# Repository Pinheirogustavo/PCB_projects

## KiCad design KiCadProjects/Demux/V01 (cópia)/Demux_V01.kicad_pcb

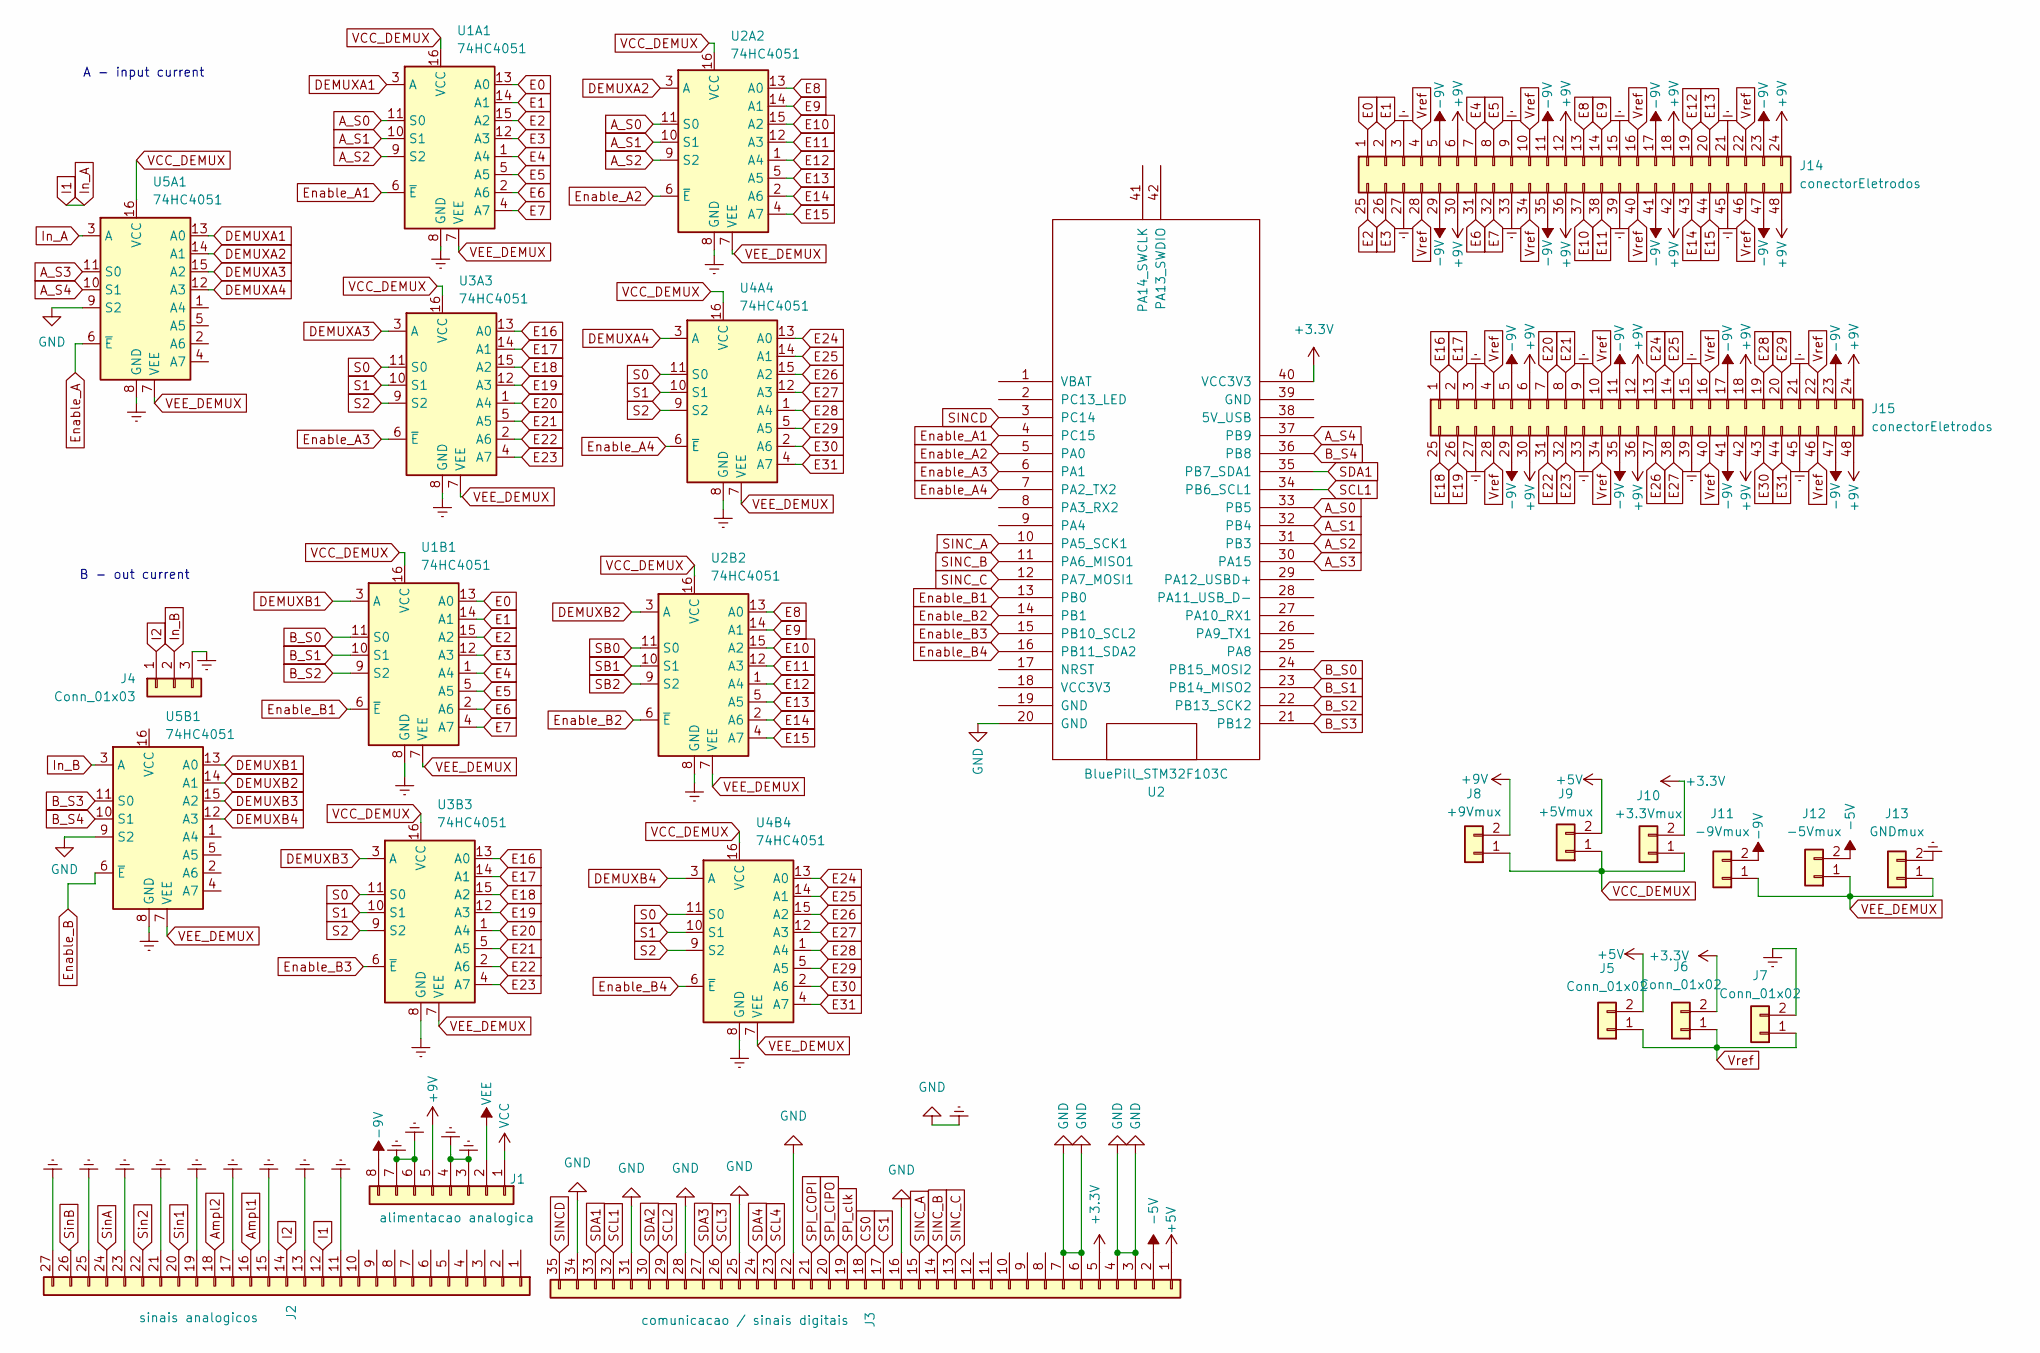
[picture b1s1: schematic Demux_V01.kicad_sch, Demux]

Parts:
J1: alimentacao analogica; PinHeader_1x08_P2.54mm_Vertical
J2: sinais analogicos; PinHeader_1x27_P2.54mm_Vertical
J3: comunicacao / sinais digitais; PinHeader_1x35_P2.54mm_Vertical
J4: Conn_01x03; PinHeader_1x03_P2.54mm_Vertical
J5, J6, J7: Conn_01x02; PinHeader_1x02_P2.54mm_Vertical
J8: +9Vmux; PinHeader_1x02_P2.54mm_Vertical
J9: +5Vmux; PinHeader_1x02_P2.54mm_Vertical
J10: +3.3Vmux; PinHeader_1x02_P2.54mm_Vertical
J11: -9Vmux; PinHeader_1x02_P2.54mm_Vertical
J12: -5Vmux; PinHeader_1x02_P2.54mm_Vertical
J13: GNDmux; PinHeader_1x02_P2.54mm_Vertical
J14, J15: conectorEletrodos; PinHeader_2x24_P2.54mm_Vertical
U1A1, U1B1, U2A2, U2B2, U3A3, U3B3, U4A4, U4B4, U5A1, U5B1: 74HC4051; N16
U2: BluePill_STM32F103C

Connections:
+3.3V: J3.5, J6.2, J10.2, U2.40 (VCC3V3)
+5V: J3.1, J5.2, J9.2
+9V: J1.5, J8.2, J14.6, J14.12, J14.18, J14.24, J14.30, J14.36, J14.42, J14.48, J15.6, J15.12, J15.18, J15.24, J15.30, J15.36, J15.42, J15.48
-5V: J3.2, J12.2
-9V: J1.8, J11.2, J14.5, J14.11, J14.17, J14.23, J14.29, J14.35, J14.41, J14.47, J15.5, J15.11, J15.17, J15.23, J15.29, J15.35, J15.41, J15.47
A_S0: U1A1.11 (S0), U2.33 (PB5), U2A2.11 (S0)
A_S1: U1A1.10 (S1), U2.32 (PB4), U2A2.10 (S1)
A_S2: U1A1.9 (S2), U2.31 (PB3), U2A2.9 (S2)
A_S3: U2.30 (PA15), U5A1.11 (S0)
A_S4: U2.37 (PB9), U5A1.10 (S1)
Ampl1: J2.16
Ampl2: J2.18
B_S0: U1B1.11 (S0), U2.24 (PB15_MOSI2)
B_S1: U1B1.10 (S1), U2.23 (PB14_MISO2)
B_S2: U1B1.9 (S2), U2.22 (PB13_SCK2)
B_S3: U2.21 (PB12), U5B1.11 (S0)
B_S4: U2.36 (PB8), U5B1.10 (S1)
CS0: J3.18
CS1: J3.17
DEMUXA1: U1A1.3 (A), U5A1.13 (A0)
DEMUXA2: U2A2.3 (A), U5A1.14 (A1)
DEMUXA3: U3A3.3 (A), U5A1.15 (A2)
DEMUXA4: U4A4.3 (A), U5A1.12 (A3)
DEMUXB1: U1B1.3 (A), U5B1.13 (A0)
DEMUXB2: U2B2.3 (A), U5B1.14 (A1)
DEMUXB3: U3B3.3 (A), U5B1.15 (A2)
DEMUXB4: U4B4.3 (A), U5B1.12 (A3)
E0: J14.1, U1A1.13 (A0), U1B1.13 (A0)
E1: J14.2, U1A1.14 (A1), U1B1.14 (A1)
E2: J14.25, U1A1.15 (A2), U1B1.15 (A2)
E3: J14.26, U1A1.12 (A3), U1B1.12 (A3)
E4: J14.7, U1A1.1 (A4), U1B1.1 (A4)
E5: J14.8, U1A1.5 (A5), U1B1.5 (A5)
E6: J14.31, U1A1.2 (A6), U1B1.2 (A6)
E7: J14.32, U1A1.4 (A7), U1B1.4 (A7)
E8: J14.13, U2A2.13 (A0), U2B2.13 (A0)
E9: J14.14, U2A2.14 (A1), U2B2.14 (A1)
E10: J14.37, U2A2.15 (A2), U2B2.15 (A2)
E11: J14.38, U2A2.12 (A3), U2B2.12 (A3)
E12: J14.19, U2A2.1 (A4), U2B2.1 (A4)
E13: J14.20, U2A2.5 (A5), U2B2.5 (A5)
E14: J14.43, U2A2.2 (A6), U2B2.2 (A6)
E15: J14.44, U2A2.4 (A7), U2B2.4 (A7)
E16: J15.1, U3A3.13 (A0), U3B3.13 (A0)
E17: J15.2, U3A3.14 (A1), U3B3.14 (A1)
E18: J15.25, U3A3.15 (A2), U3B3.15 (A2)
E19: J15.26, U3A3.12 (A3), U3B3.12 (A3)
E20: J15.7, U3A3.1 (A4), U3B3.1 (A4)
E21: J15.8, U3A3.5 (A5), U3B3.5 (A5)
E22: J15.31, U3A3.2 (A6), U3B3.2 (A6)
E23: J15.32, U3A3.4 (A7), U3B3.4 (A7)
E24: J15.13, U4A4.13 (A0), U4B4.13 (A0)
E25: J15.14, U4A4.14 (A1), U4B4.14 (A1)
E26: J15.37, U4A4.15 (A2), U4B4.15 (A2)
E27: J15.38, U4A4.12 (A3), U4B4.12 (A3)
E28: J15.19, U4A4.1 (A4), U4B4.1 (A4)
E29: J15.20, U4A4.5 (A5), U4B4.5 (A5)
E30: J15.43, U4A4.2 (A6), U4B4.2 (A6)
E31: J15.44, U4A4.4 (A7), U4B4.4 (A7)
Earth: J1.3, J1.4, J1.6, J1.7, J2.11, J2.13, J2.15, J2.17, J2.19, J2.21, J2.23, J2.25, J2.27, J3.3, J3.4, J3.6, J3.7, J3.16, J3.22, J3.25, J3.28, J3.31, J3.34, J4.3, J7.2, J13.2, J14.3, J14.9, J14.15, J14.21, J14.27, J14.33, J14.39, J14.45, J15.3, J15.9, J15.15, J15.21, J15.27, J15.33, J15.39, J15.45, U1A1.8 (GND), U1B1.8 (GND), U2.20 (GND), U2A2.8 (GND), U2B2.8 (GND), U3A3.8 (GND), U3B3.8 (GND), U4A4.8 (GND), U4B4.8 (GND), U5A1.8 (GND), U5A1.9 (S2), U5B1.8 (GND), U5B1.9 (S2)
Enable_A: U5A1.6 (~E)
Enable_A1: U1A1.6 (~E), U2.4 (PC15)
Enable_A2: U2.5 (PA0), U2A2.6 (~E)
Enable_A3: U2.6 (PA1), U3A3.6 (~E)
Enable_A4: U2.7 (PA2_TX2), U4A4.6 (~E)
Enable_B: U5B1.6 (~E)
Enable_B1: U1B1.6 (~E), U2.13 (PB0)
Enable_B2: U2.14 (PB1), U2B2.6 (~E)
Enable_B3: U2.15 (PB10_SCL2), U3B3.6 (~E)
Enable_B4: U2.16 (PB11_SDA2), U4B4.6 (~E)
I1: J2.12, U5A1.3 (A)
I2: J2.14, J4.1
In_B: J4.2, U5B1.3 (A)
S0: U3A3.11 (S0), U3B3.11 (S0), U4A4.11 (S0), U4B4.11 (S0)
S1: U3A3.10 (S1), U3B3.10 (S1), U4A4.10 (S1), U4B4.10 (S1)
S2: U3A3.9 (S2), U3B3.9 (S2), U4A4.9 (S2), U4B4.9 (S2)
SB0: U2B2.11 (S0)
SB1: U2B2.10 (S1)
SB2: U2B2.9 (S2)
SCL1: J3.32, U2.34 (PB6_SCL1)
SCL2: J3.29
SCL3: J3.26
SCL4: J3.23
SDA1: J3.33, U2.35 (PB7_SDA1)
SDA2: J3.30
SDA3: J3.27
SDA4: J3.24
SINCD: J3.35, U2.3 (PC14)
SINC_A: J3.15, U2.10 (PA5_SCK1)
SINC_B: J3.14, U2.11 (PA6_MISO1)
SINC_C: J3.13, U2.12 (PA7_MOSI1)
SPI_CIPO: J3.20
SPI_COPI: J3.21
SPI_clk: J3.19
Sin1: J2.20
Sin2: J2.22
SinA: J2.24
SinB: J2.26
VCC: J1.1
VCC_DEMUX: J8.1, J9.1, J10.1, U1A1.16 (VCC), U1B1.16 (VCC), U2A2.16 (VCC), U2B2.16 (VCC), U3A3.16 (VCC), U3B3.16 (VCC), U4A4.16 (VCC), U4B4.16 (VCC), U5A1.16 (VCC)
VEE: J1.2
VEE_DEMUX: J11.1, J12.1, J13.1, U1A1.7 (VEE), U1B1.7 (VEE), U2A2.7 (VEE), U2B2.7 (VEE), U3A3.7 (VEE), U3B3.7 (VEE), U4A4.7 (VEE), U4B4.7 (VEE), U5A1.7 (VEE), U5B1.7 (VEE)
Vref: J5.1, J6.1, J7.1, J14.4, J14.10, J14.16, J14.22, J14.28, J14.34, J14.40, J14.46, J15.4, J15.10, J15.16, J15.22, J15.28, J15.34, J15.40, J15.46

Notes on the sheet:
A - input current
B - out current

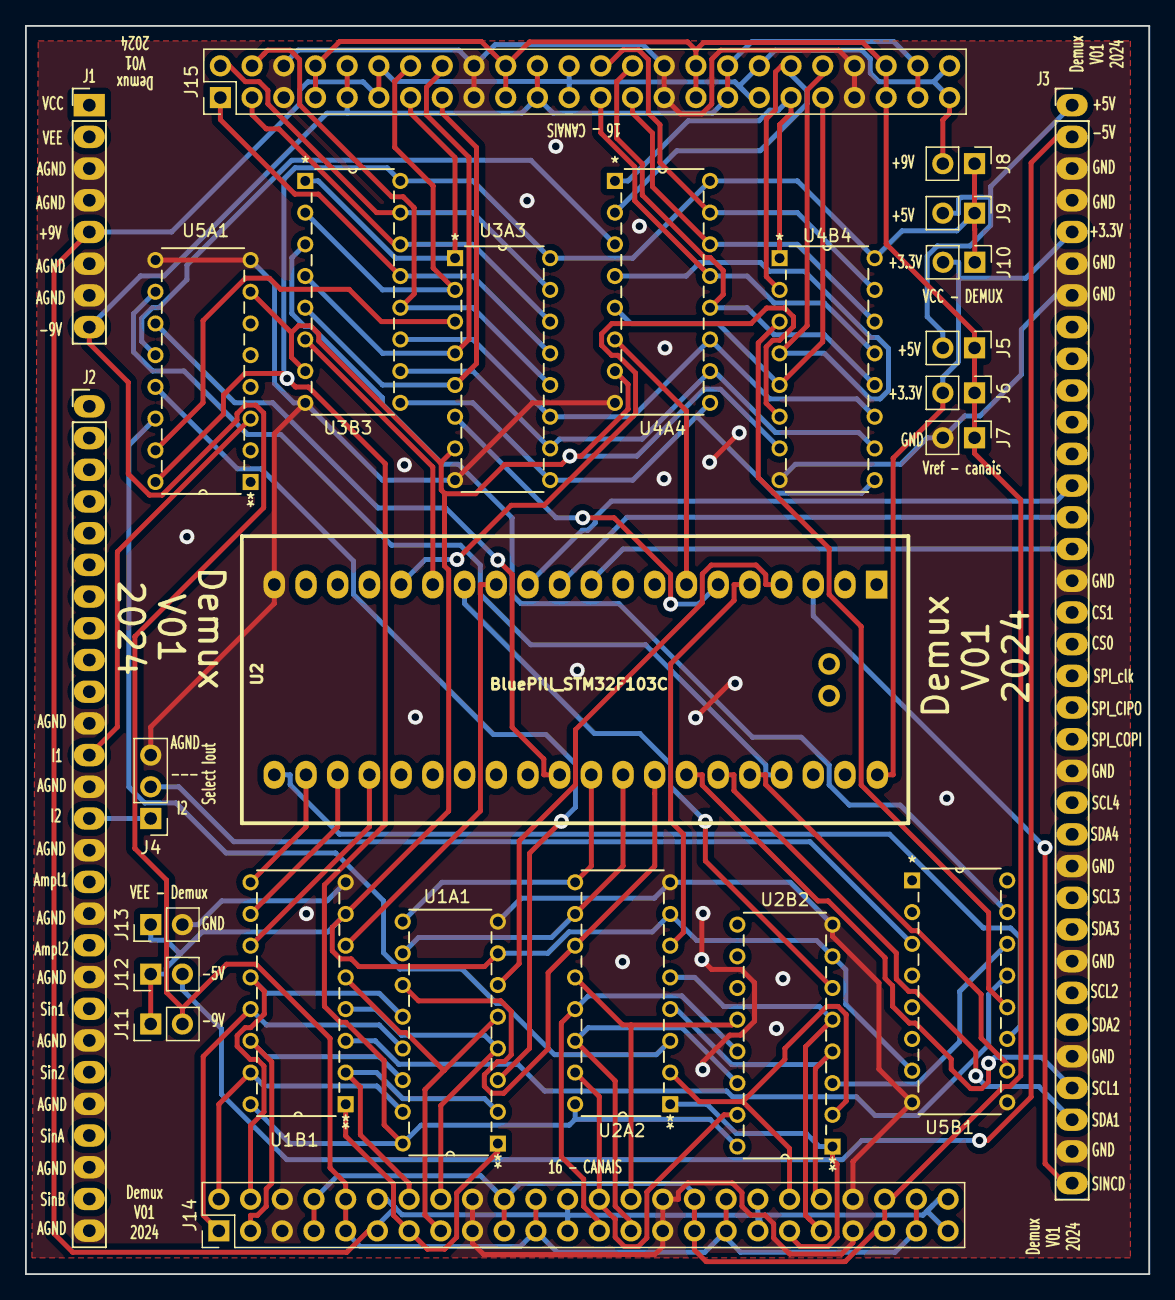
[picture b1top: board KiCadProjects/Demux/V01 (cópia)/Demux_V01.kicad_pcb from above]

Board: 2 copper layers, 90.0 x 100.0 mm, 26 parts (0 on the bottom side), 79 nets.

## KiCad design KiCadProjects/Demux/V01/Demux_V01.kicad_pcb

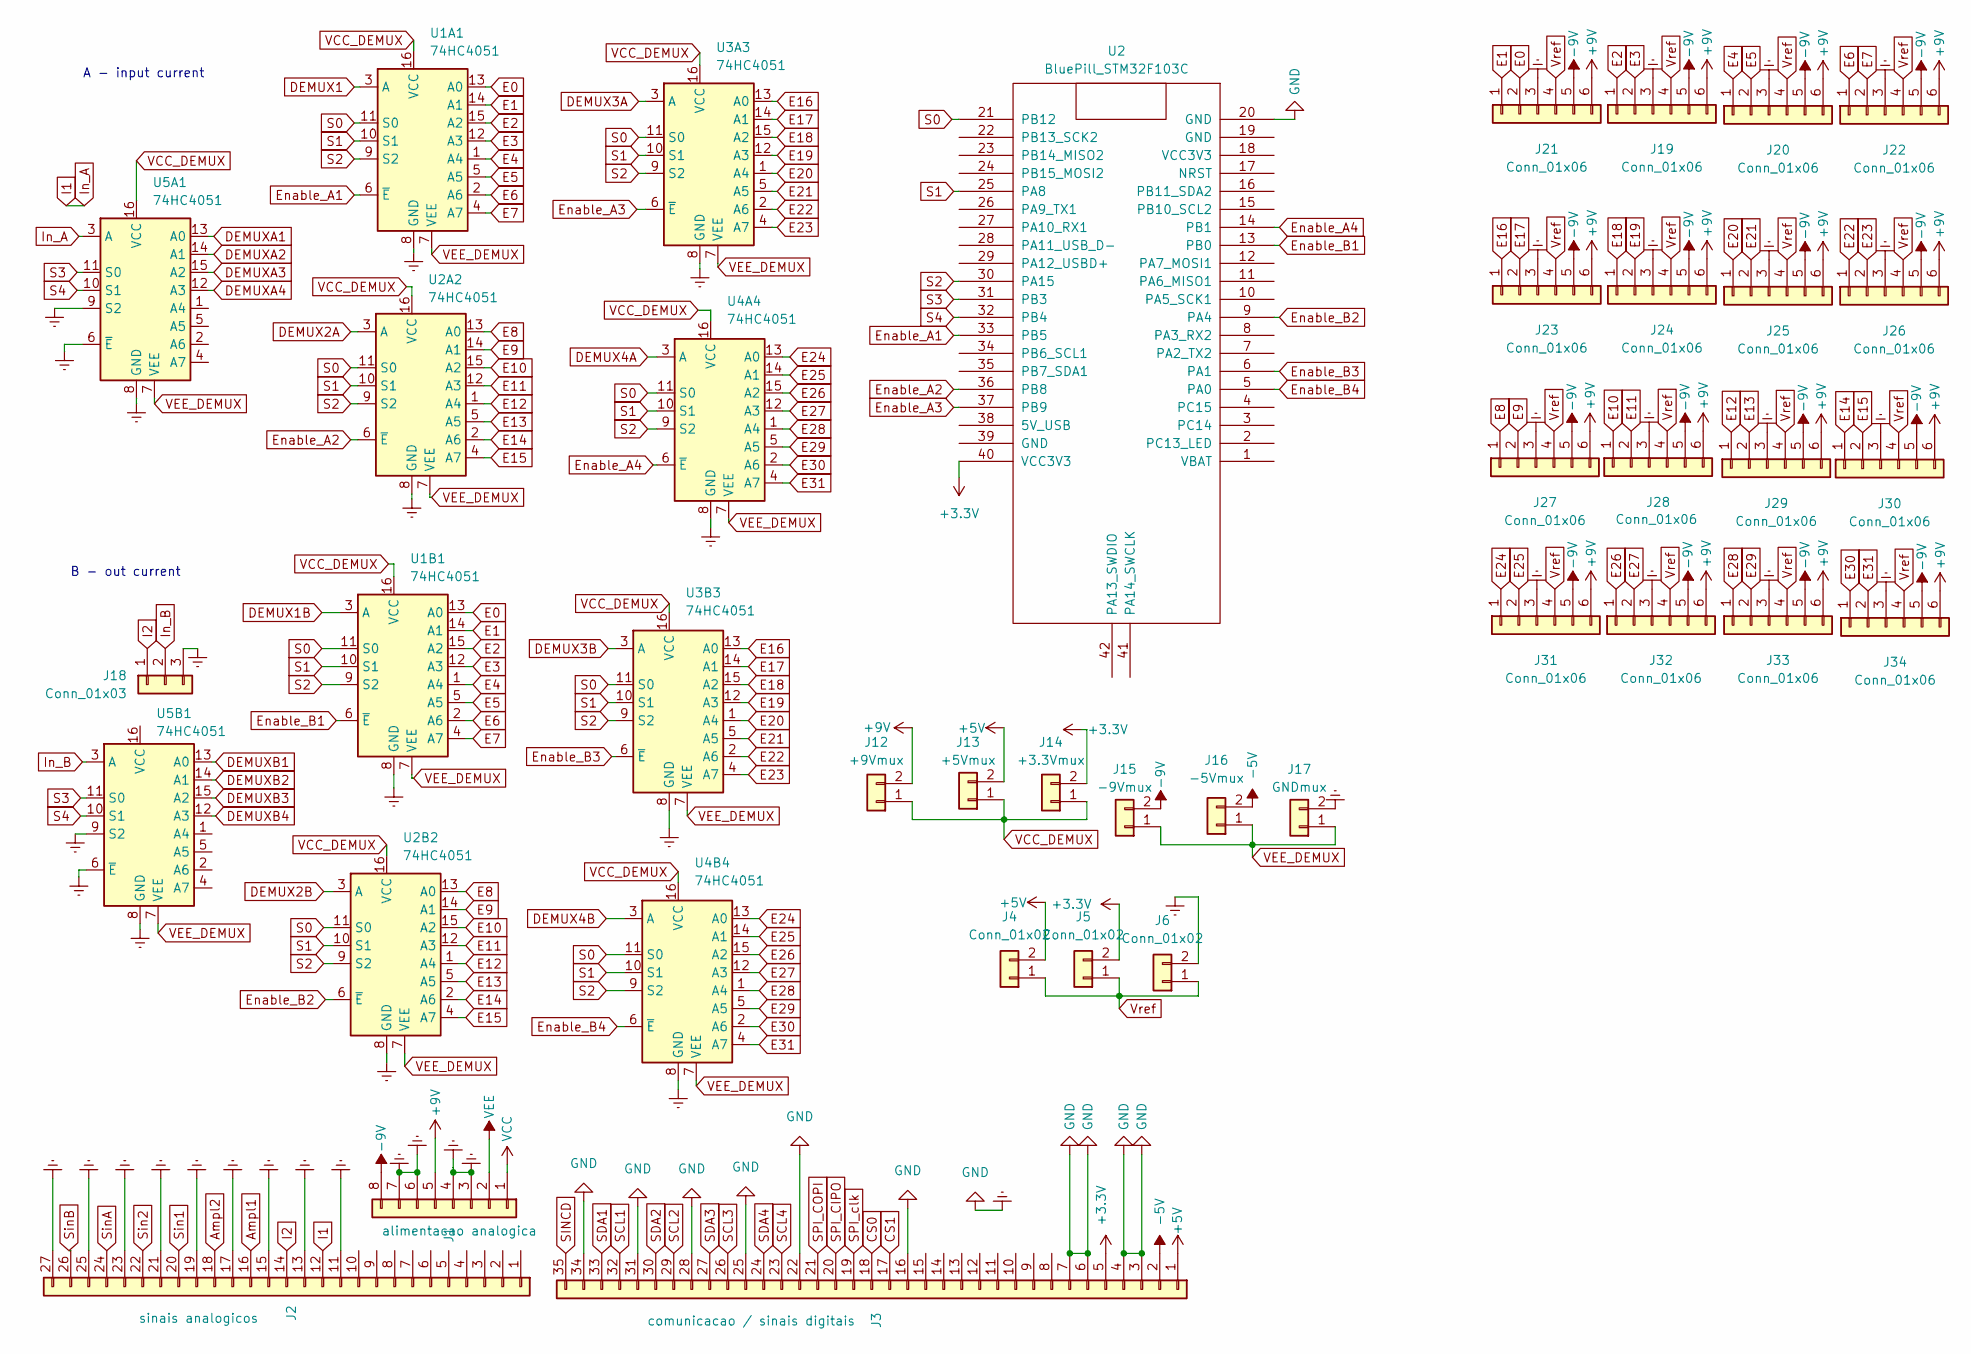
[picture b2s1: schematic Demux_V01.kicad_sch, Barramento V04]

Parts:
J1: alimentacao analogica; PinHeader_1x08_P2.54mm_Vertical
J2: sinais analogicos; PinHeader_1x27_P2.54mm_Vertical
J3: comunicacao / sinais digitais; PinHeader_1x35_P2.54mm_Vertical
J4, J5, J6: Conn_01x02; PinHeader_1x02_P2.54mm_Vertical
J12: +9Vmux; PinHeader_1x02_P2.54mm_Vertical
J13: +5Vmux; PinHeader_1x02_P2.54mm_Vertical
J14: +3.3Vmux; PinHeader_1x02_P2.54mm_Vertical
J15: -9Vmux; PinHeader_1x02_P2.54mm_Vertical
J16: -5Vmux; PinHeader_1x02_P2.54mm_Vertical
J17: GNDmux; PinHeader_1x02_P2.54mm_Vertical
J18: Conn_01x03; PinHeader_1x03_P2.54mm_Vertical
J19, J20, J21, J22, J23, J24, J25, J26, J27, J28, J29, J30, J31, J32, J33, J34: Conn_01x06; PinHeader_1x06_P2.54mm_Horizontal
U1A1, U1B1, U2A2, U2B2, U3A3, U3B3, U4A4, U4B4, U5A1, U5B1: 74HC4051; N16
U2: BluePill_STM32F103C

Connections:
+3.3V: J3.5, J5.2, J14.2, U2.40 (VCC3V3)
+5V: J3.1, J4.2, J13.2
+9V: J1.5, J12.2, J19.6, J20.6, J21.6, J22.6, J23.6, J24.6, J25.6, J26.6, J27.6, J28.6, J29.6, J30.6, J31.6, J32.6, J33.6, J34.6
-5V: J3.2, J16.2
-9V: J1.8, J15.2, J19.5, J20.5, J21.5, J22.5, J23.5, J24.5, J25.5, J26.5, J27.5, J28.5, J29.5, J30.5, J31.5, J32.5, J33.5, J34.5
Ampl1: J2.16
Ampl2: J2.18
CS0: J3.18
CS1: J3.17
DEMUX1: U1A1.3 (A)
DEMUX1B: U1B1.3 (A)
DEMUX2A: U2A2.3 (A)
DEMUX2B: U2B2.3 (A)
DEMUX3A: U3A3.3 (A)
DEMUX3B: U3B3.3 (A)
DEMUX4A: U4A4.3 (A)
DEMUX4B: U4B4.3 (A)
DEMUXA1: U5A1.13 (A0)
DEMUXA2: U5A1.14 (A1)
DEMUXA3: U5A1.15 (A2)
DEMUXA4: U5A1.12 (A3)
DEMUXB1: U5B1.13 (A0)
DEMUXB2: U5B1.14 (A1)
DEMUXB3: U5B1.15 (A2)
DEMUXB4: U5B1.12 (A3)
E0: J21.2, U1A1.13 (A0), U1B1.13 (A0)
E1: J21.1, U1A1.14 (A1), U1B1.14 (A1)
E2: J19.1, U1A1.15 (A2), U1B1.15 (A2)
E3: J19.2, U1A1.12 (A3), U1B1.12 (A3)
E4: J20.1, U1A1.1 (A4), U1B1.1 (A4)
E5: J20.2, U1A1.5 (A5), U1B1.5 (A5)
E6: J22.1, U1A1.2 (A6), U1B1.2 (A6)
E7: J22.2, U1A1.4 (A7), U1B1.4 (A7)
E8: J27.1, U2A2.13 (A0), U2B2.13 (A0)
E9: J27.2, U2A2.14 (A1), U2B2.14 (A1)
E10: J28.1, U2A2.15 (A2), U2B2.15 (A2)
E11: J28.2, U2A2.12 (A3), U2B2.12 (A3)
E12: J29.1, U2A2.1 (A4), U2B2.1 (A4)
E13: J29.2, U2A2.5 (A5), U2B2.5 (A5)
E14: J30.1, U2A2.2 (A6), U2B2.2 (A6)
E15: J30.2, U2A2.4 (A7), U2B2.4 (A7)
E16: J23.1, U3A3.13 (A0), U3B3.13 (A0)
E17: J23.2, U3A3.14 (A1), U3B3.14 (A1)
E18: J24.1, U3A3.15 (A2), U3B3.15 (A2)
E19: J24.2, U3A3.12 (A3), U3B3.12 (A3)
E20: J25.1, U3A3.1 (A4), U3B3.1 (A4)
E21: J25.2, U3A3.5 (A5), U3B3.5 (A5)
E22: J26.1, U3A3.2 (A6), U3B3.2 (A6)
E23: J26.2, U3A3.4 (A7), U3B3.4 (A7)
E24: J31.1, U4A4.13 (A0), U4B4.13 (A0)
E25: J31.2, U4A4.14 (A1), U4B4.14 (A1)
E26: J32.1, U4A4.15 (A2), U4B4.15 (A2)
E27: J32.2, U4A4.12 (A3), U4B4.12 (A3)
E28: J33.1, U4A4.1 (A4), U4B4.1 (A4)
E29: J33.2, U4A4.5 (A5), U4B4.5 (A5)
E30: J34.1, U4A4.2 (A6), U4B4.2 (A6)
E31: J34.2, U4A4.4 (A7), U4B4.4 (A7)
Earth: J1.3, J1.4, J1.6, J1.7, J2.11, J2.13, J2.15, J2.17, J2.19, J2.21, J2.23, J2.25, J2.27, J3.3, J3.4, J3.6, J3.7, J3.16, J3.22, J3.25, J3.28, J3.31, J3.34, J6.2, J17.2, J18.3, J19.3, J20.3, J21.3, J22.3, J23.3, J24.3, J25.3, J26.3, J27.3, J28.3, J29.3, J30.3, J31.3, J32.3, J33.3, J34.3, U1A1.8 (GND), U1B1.8 (GND), U2.20 (GND), U2A2.8 (GND), U2B2.8 (GND), U3A3.8 (GND), U3B3.8 (GND), U4A4.8 (GND), U4B4.8 (GND), U5A1.6 (~E), U5A1.8 (GND), U5A1.9 (S2), U5B1.6 (~E), U5B1.8 (GND), U5B1.9 (S2)
Enable_A1: U1A1.6 (~E), U2.33 (PB5)
Enable_A2: U2.36 (PB8), U2A2.6 (~E)
Enable_A3: U2.37 (PB9), U3A3.6 (~E)
Enable_A4: U2.14 (PB1), U4A4.6 (~E)
Enable_B1: U1B1.6 (~E), U2.13 (PB0)
Enable_B2: U2.9 (PA4), U2B2.6 (~E)
Enable_B3: U2.6 (PA1), U3B3.6 (~E)
Enable_B4: U2.5 (PA0), U4B4.6 (~E)
I1: J2.12, U5A1.3 (A)
I2: J2.14, J18.1
In_B: J18.2, U5B1.3 (A)
S0: U1A1.11 (S0), U1B1.11 (S0), U2.21 (PB12), U2A2.11 (S0), U2B2.11 (S0), U3A3.11 (S0), U3B3.11 (S0), U4A4.11 (S0), U4B4.11 (S0)
S1: U1A1.10 (S1), U1B1.10 (S1), U2.25 (PA8), U2A2.10 (S1), U2B2.10 (S1), U3A3.10 (S1), U3B3.10 (S1), U4A4.10 (S1), U4B4.10 (S1)
S2: U1A1.9 (S2), U1B1.9 (S2), U2.30 (PA15), U2A2.9 (S2), U2B2.9 (S2), U3A3.9 (S2), U3B3.9 (S2), U4A4.9 (S2), U4B4.9 (S2)
S3: U2.31 (PB3), U5A1.11 (S0), U5B1.11 (S0)
S4: U2.32 (PB4), U5A1.10 (S1), U5B1.10 (S1)
SCL1: J3.32
SCL2: J3.29
SCL3: J3.26
SCL4: J3.23
SDA1: J3.33
SDA2: J3.30
SDA3: J3.27
SDA4: J3.24
SINCD: J3.35
SPI_CIPO: J3.20
SPI_COPI: J3.21
SPI_clk: J3.19
Sin1: J2.20
Sin2: J2.22
SinA: J2.24
SinB: J2.26
VCC: J1.1
VCC_DEMUX: J12.1, J13.1, J14.1, U1A1.16 (VCC), U1B1.16 (VCC), U2A2.16 (VCC), U2B2.16 (VCC), U3A3.16 (VCC), U3B3.16 (VCC), U4A4.16 (VCC), U4B4.16 (VCC), U5A1.16 (VCC)
VEE: J1.2
VEE_DEMUX: J15.1, J16.1, J17.1, U1A1.7 (VEE), U1B1.7 (VEE), U2A2.7 (VEE), U2B2.7 (VEE), U3A3.7 (VEE), U3B3.7 (VEE), U4A4.7 (VEE), U4B4.7 (VEE), U5A1.7 (VEE), U5B1.7 (VEE)
Vref: J4.1, J5.1, J6.1, J19.4, J20.4, J21.4, J22.4, J23.4, J24.4, J25.4, J26.4, J27.4, J28.4, J29.4, J30.4, J31.4, J32.4, J33.4, J34.4

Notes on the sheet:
A - input current
B - out current

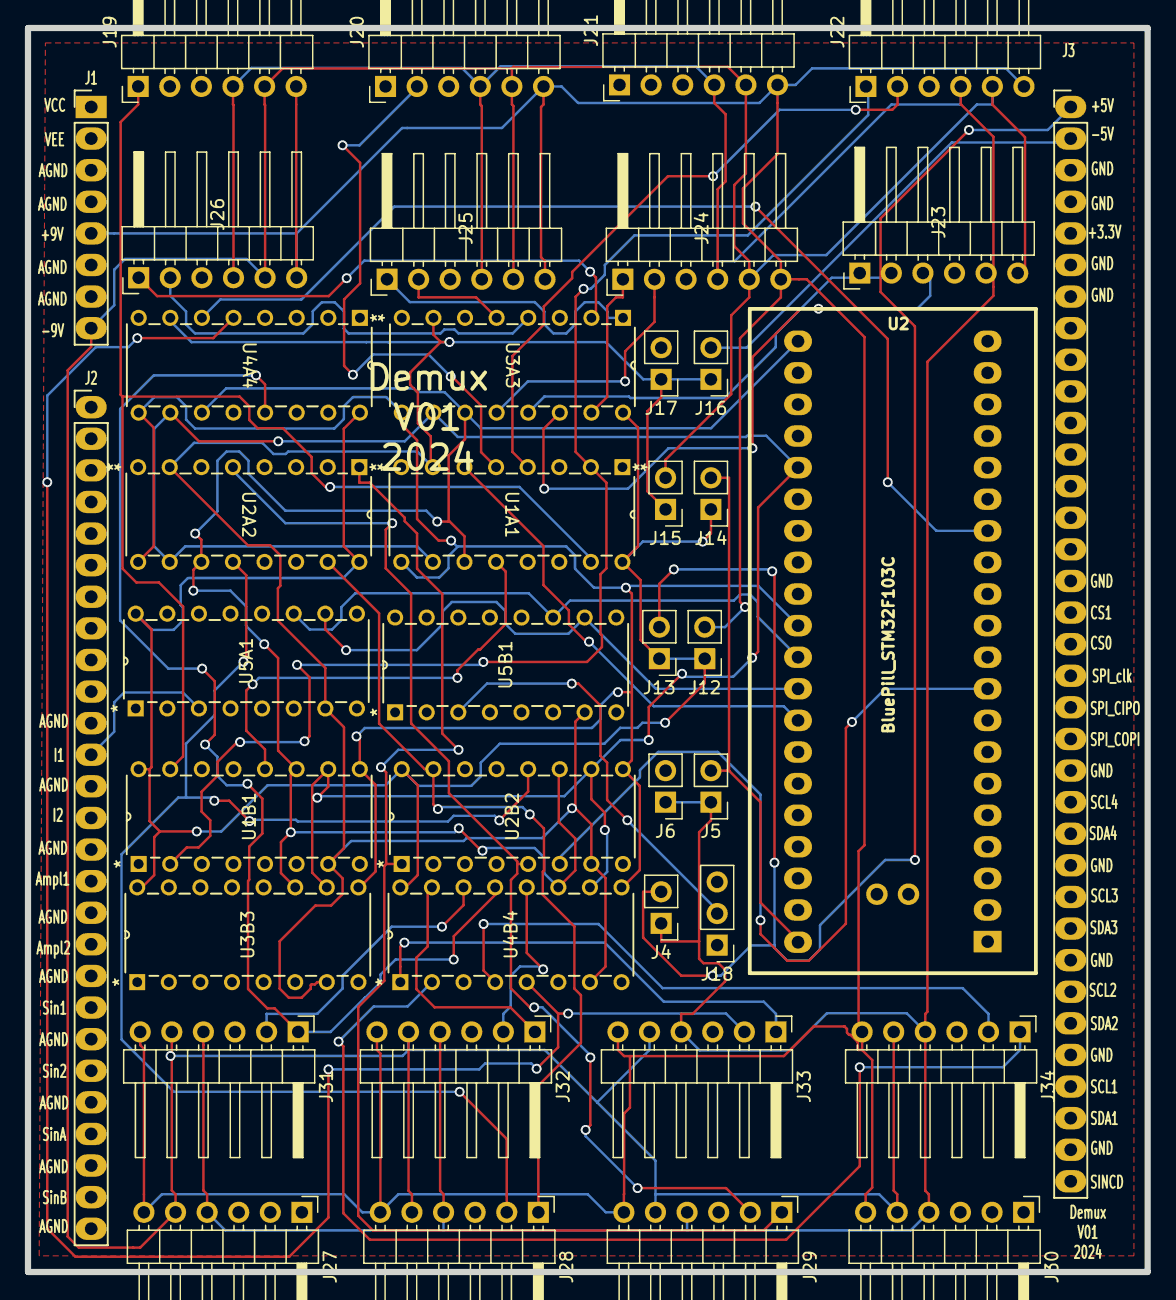
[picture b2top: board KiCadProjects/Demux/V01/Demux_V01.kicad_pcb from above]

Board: 2 copper layers, 90.0 x 100.0 mm, 40 parts (0 on the bottom side), 57 nets.

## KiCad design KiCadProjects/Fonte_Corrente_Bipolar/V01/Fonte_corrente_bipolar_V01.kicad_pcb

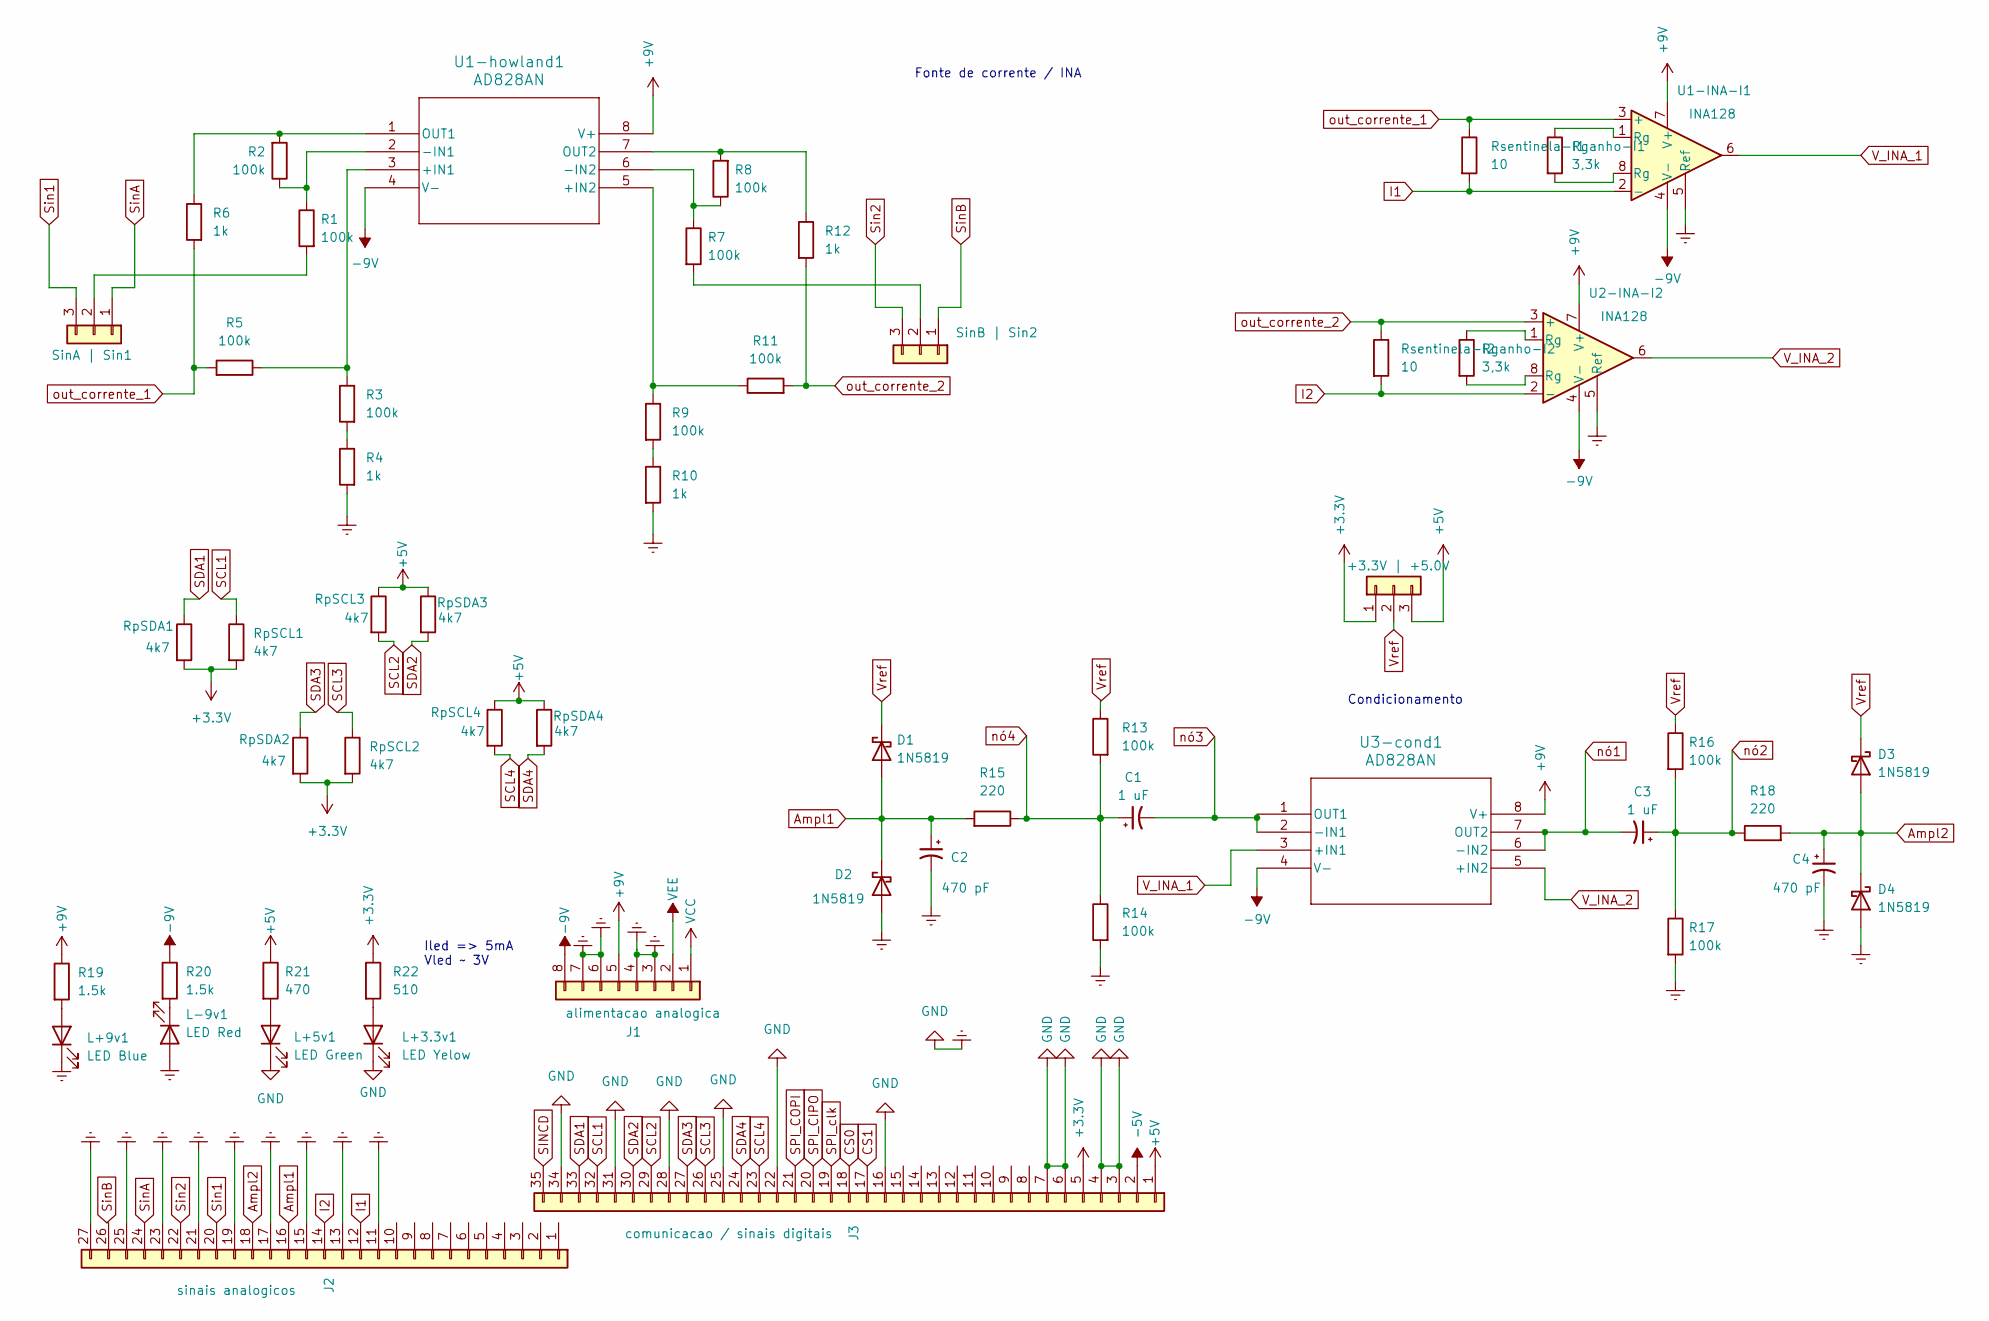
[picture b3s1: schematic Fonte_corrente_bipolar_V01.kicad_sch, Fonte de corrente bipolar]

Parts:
C1, C3: 1 uF; CP_Radial_D5.0mm_P2.50mm
C2, C4: 470 pF; CP_Radial_D5.0mm_P2.50mm
D1, D2, D3, D4: 1N5819; D_DO-41_SOD81_P10.16mm_Horizontal
J1: alimentacao analogica; PinHeader_1x08_P2.54mm_Vertical
J2: sinais analogicos; PinHeader_1x27_P2.54mm_Vertical
J3: comunicacao / sinais digitais; PinHeader_1x35_P2.54mm_Vertical
J4: SinA | Sin1; PinHeader_1x03_P2.54mm_Vertical
J5: SinB | Sin2; PinHeader_1x03_P2.54mm_Vertical
J7: +3.3V | +5.0V; PinHeader_1x03_P2.54mm_Vertical
L+3.3v1: LED Yelow; LED_D5.0mm
L+5v1: LED Green; LED_D5.0mm
L+9v1: LED Blue; LED_D5.0mm
L-9v1: LED Red; LED_D5.0mm
R1, R2, R3, R5, R7, R8, R9, R11, R13, R14, R16, R17: 100k; R_Axial_DIN0207_L6.3mm_D2.5mm_P7.62mm_Horizontal
R4, R6, R10, R12: 1k; R_Axial_DIN0207_L6.3mm_D2.5mm_P7.62mm_Horizontal
R15, R18: 220; R_Axial_DIN0207_L6.3mm_D2.5mm_P7.62mm_Horizontal
R19, R20: 1.5k; R_Axial_DIN0207_L6.3mm_D2.5mm_P7.62mm_Horizontal
R21: 470; R_Axial_DIN0207_L6.3mm_D2.5mm_P7.62mm_Horizontal
R22: 510; R_Axial_DIN0207_L6.3mm_D2.5mm_P7.62mm_Horizontal
Rganho-I1, Rganho-I2: 3,3k; R_Axial_DIN0207_L6.3mm_D2.5mm_P7.62mm_Horizontal
RpSCL1, RpSCL2, RpSCL3, RpSCL4: 4k7; R_Axial_DIN0207_L6.3mm_D2.5mm_P7.62mm_Horizontal
RpSDA1, RpSDA2, RpSDA3, RpSDA4: 4k7; R_Axial_DIN0207_L6.3mm_D2.5mm_P7.62mm_Horizontal
Rsentinela-I1, Rsentinela-I2: 10; R_Axial_DIN0207_L6.3mm_D2.5mm_P7.62mm_Horizontal
U1-INA-I1, U2-INA-I2: INA128; DIP-8_W7.62mm
U1-howland1, U3-cond1: AD828AN; AD828

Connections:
+3.3V: J3.5, J7.1, R22.1, RpSCL1.2, RpSCL2.2, RpSDA1.2, RpSDA2.2
+5V: J3.1, J7.3, R21.1, RpSCL3.1, RpSCL4.1, RpSDA3.1, RpSDA4.1
+9V: J1.5, R19.1, U1-INA-I1.7 (V+), U1-howland1.8 (V+), U2-INA-I2.7 (V+), U3-cond1.8 (V+)
-5V: J3.2
-9V: J1.8, R20.1, U1-INA-I1.4 (V-), U1-howland1.4 (V-), U2-INA-I2.4 (V-), U3-cond1.4 (V-)
Ampl1: C2.1, D1.2 (A), D2.1 (K), J2.16, R15.2
Ampl2: C4.1, D3.2 (A), D4.1 (K), J2.18, R18.2
CS0: J3.18
CS1: J3.17
Earth: C2.2, C4.2, D2.2 (A), D4.2 (A), J1.3, J1.4, J1.6, J1.7, J2.11, J2.13, J2.15, J2.17, J2.19, J2.21, J2.23, J2.25, J2.27, J3.3, J3.4, J3.6, J3.7, J3.16, J3.22, J3.25, J3.28, J3.31, J3.34, L+3.3v1.1 (K), L+5v1.1 (K), L+9v1.1 (K), L-9v1.2 (A), R4.2, R10.2, R14.2, R17.2, U1-INA-I1.5 (Ref), U2-INA-I2.5 (Ref)
I1: J2.12, Rsentinela-I1.2, U1-INA-I1.2 (-)
I2: J2.14, Rsentinela-I2.2, U2-INA-I2.2 (-)
unnamed: J4.2, R1.2
unnamed: J5.2, R7.2
unnamed: L+3.3v1.2 (A), R22.2
unnamed: L+5v1.2 (A), R21.2
unnamed: L+9v1.2 (A), R19.2
unnamed: L-9v1.1 (K), R20.2
unnamed: R3.2, R4.1
unnamed: R9.2, R10.1
unnamed: Rganho-I1.1, U1-INA-I1.1 (Rg)
unnamed: Rganho-I1.2, U1-INA-I1.8 (Rg)
unnamed: Rganho-I2.1, U2-INA-I2.1 (Rg)
unnamed: Rganho-I2.2, U2-INA-I2.8 (Rg)
unnamed: R3.1, R5.1, U1-howland1.3 (+IN1)
unnamed: R9.1, R11.1, U1-howland1.5 (+IN2)
unnamed: R1.1, R2.1, U1-howland1.2 (-IN1)
unnamed: R7.1, R8.1, U1-howland1.6 (-IN2)
unnamed: R2.2, R6.1, U1-howland1.1 (OUT1)
unnamed: R8.2, R12.1, U1-howland1.7 (OUT2)
SCL1: J3.32, RpSCL1.1
SCL2: J3.29, RpSCL3.2
SCL3: J3.26, RpSCL2.1
SCL4: J3.23, RpSCL4.2
SDA1: J3.33, RpSDA1.1
SDA2: J3.30, RpSDA3.2
SDA3: J3.27, RpSDA2.1
SDA4: J3.24, RpSDA4.2
SINCD: J3.35
SPI_CIPO: J3.20
SPI_COPI: J3.21
SPI_clk: J3.19
Sin1: J2.20, J4.3
Sin2: J2.22, J5.3
SinA: J2.24, J4.1
SinB: J2.26, J5.1
VCC: J1.1
VEE: J1.2
V_INA_1: U1-INA-I1.6, U3-cond1.3 (+IN1)
V_INA_2: U2-INA-I2.6, U3-cond1.5 (+IN2)
Vref: D1.1 (K), D3.1 (K), J7.2, R13.1, R16.1
nó1: C3.2, U3-cond1.6 (-IN2), U3-cond1.7 (OUT2)
nó2: C3.1, R16.2, R17.1, R18.1
nó3: C1.2, U3-cond1.1 (OUT1), U3-cond1.2 (-IN1)
nó4: C1.1, R13.2, R14.1, R15.1
out_corrente_1: R5.2, R6.2, Rsentinela-I1.1, U1-INA-I1.3 (+)
out_corrente_2: R11.2, R12.2, Rsentinela-I2.1, U2-INA-I2.3 (+)

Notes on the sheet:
Fonte de corrente / INA
Iled => 5mA Vled ~ 3V
Condicionamento

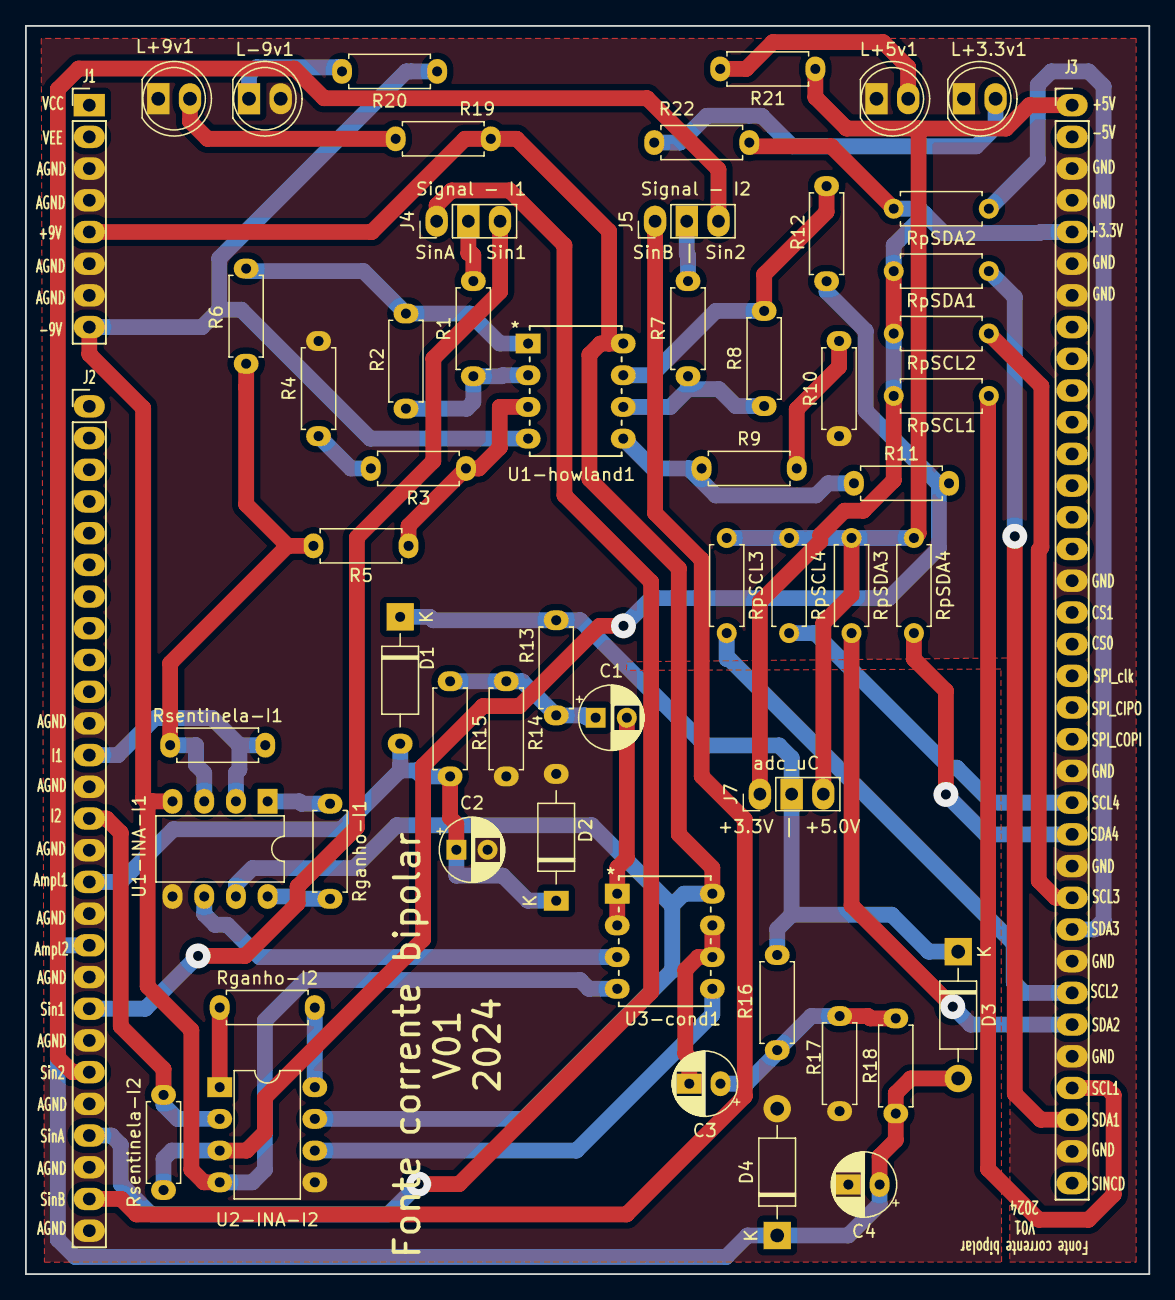
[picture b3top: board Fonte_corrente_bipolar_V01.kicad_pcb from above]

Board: 2 copper layers, 90.0 x 100.0 mm, 56 parts (0 on the bottom side), 48 nets.
